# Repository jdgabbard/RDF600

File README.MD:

# RDF-600
 RDF-600 Floppy Adapter for MSX Computers.

***Based on the TDC-600***

This is a clone of the TDC-600 Disk Adadpter for MSX Computers redesigned for a more compact footprint.  This should fit inside standard MSX cartridge shells that have been modified to allow for the floppy ribbon cable.

The board is compatible with the standard TDC-600 firmware.  Or, if using an imported machine in the US or UK, it can be used with the provided firmware which has been patched for the English Language.

The Original Source Code for the PCB, and a working disassembly of it, can be found here:  https://github.com/jdgabbard/TDC-600-Source-Code

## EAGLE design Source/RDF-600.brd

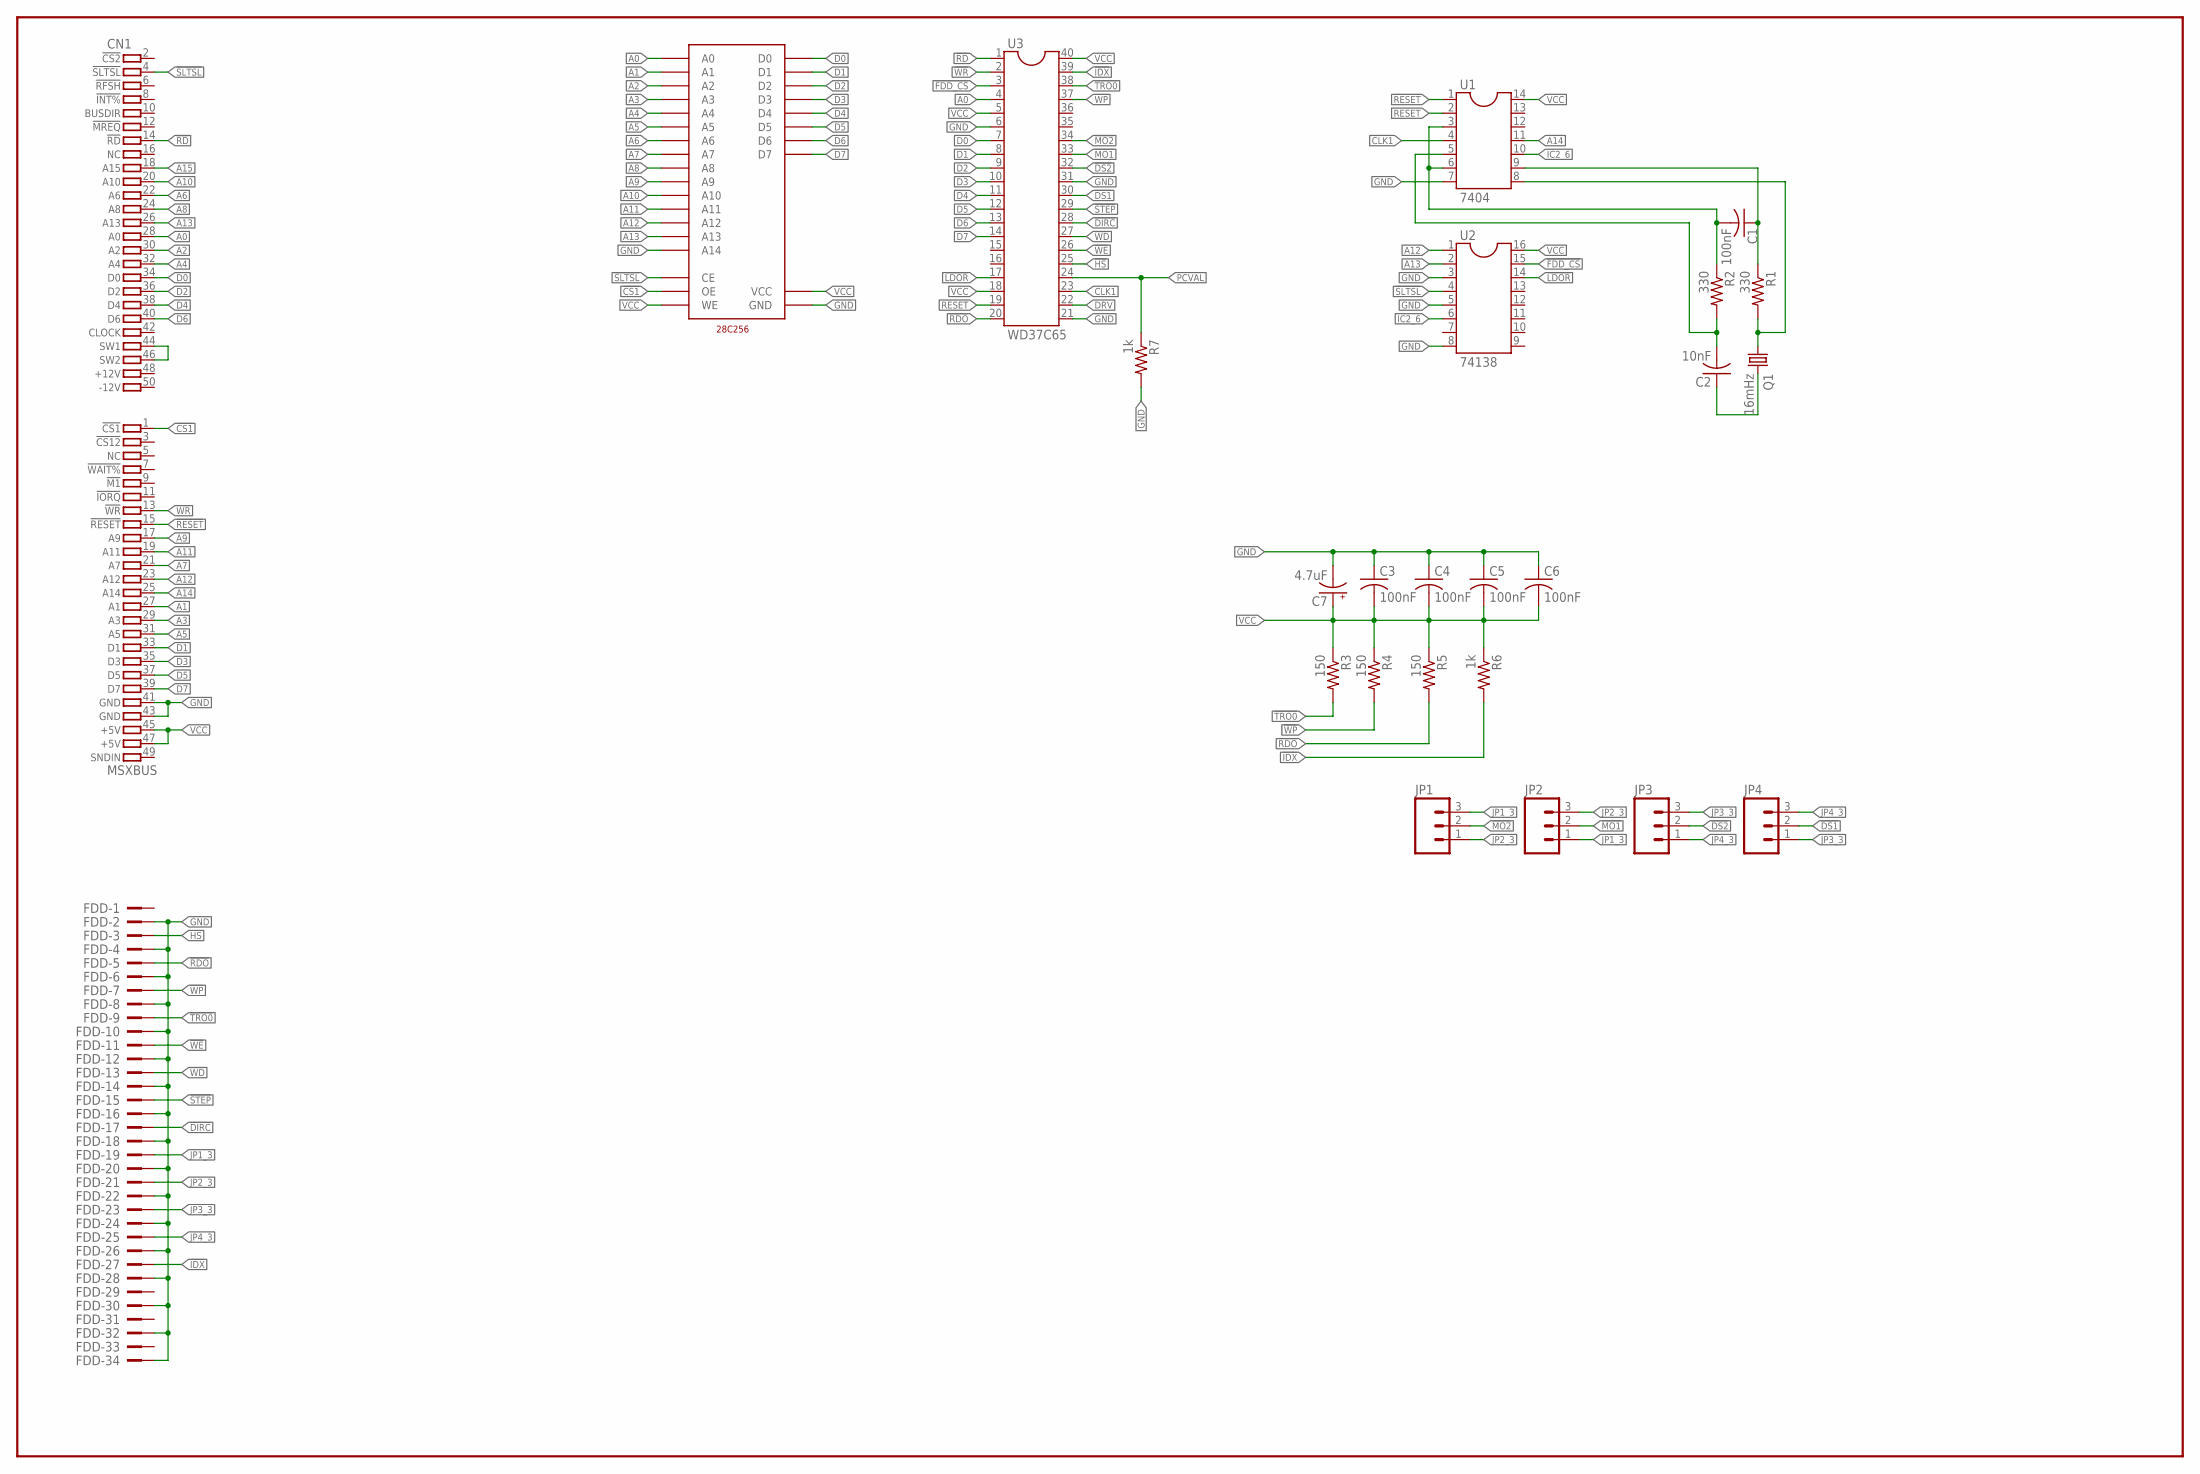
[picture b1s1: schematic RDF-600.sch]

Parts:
28C256: 28C256; DIP28
C1, C3, C4, C5, C6: 100nF; C025-025X050
C2: 10nF; C025-025X050
C7: 4.7uF; E2,5-6E
CN1: MSXBUS; MSXBUS_EDGECONN
FDD: 2534-5; PAK100/2500-5-34
JP1, JP2, JP3, JP4: M03PTH; 1X03
Q1: 16mHz; HC49/S
R1, R2: 330; 0207/7
R3, R4, R5: 150; 0207/7
R6, R7: 1k; 0207/7
U1: 7404; DIL14
U2: 74138; DIL16
U3: WD37C65; DIL40

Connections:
!CS1: 28C256.P$22 (OE), CN1.1 (1.!CS1)
!DIRC: FDD.17, U3.28
!DS1: JP4.2, U3.30
!DS2: JP3.2, U3.32
!FDD_CS: U2.15, U3.3
!HS: FDD.3, U3.25
!IDX: FDD.27, R6.2, U3.39
!LDOR: U2.14, U3.17
!MO1: JP2.2, U3.33
!MO2: JP1.2, U3.34
!RD: CN1.14 (14.!RD), U3.1
!RDO: FDD.5, R5.2, U3.20
!RESET: CN1.15 (15.!RESET), U1.1
!SLTSL: 28C256.P$20 (CE), CN1.4 (4.!SLTSL), U2.4
!STEP: FDD.15, U3.29
!TRO0: FDD.9, R3.2, U3.38
!WD: FDD.13, U3.27
!WE: FDD.11, U3.26
!WP: FDD.7, R4.2, U3.37
!WR: CN1.13 (13.!WR), U3.2
A0: 28C256.P$10 (A0), CN1.28 (28.A0), U3.4
A1: 28C256.P$9 (A1), CN1.27 (27.A1)
A2: 28C256.P$8 (A2), CN1.30 (30.A2)
A3: 28C256.P$7 (A3), CN1.29 (29.A3)
A4: 28C256.P$6 (A4), CN1.32 (32.A4)
A5: 28C256.P$5 (A5), CN1.31 (31.A5)
A6: 28C256.P$4 (A6), CN1.22 (22.A6)
A7: 28C256.P$3 (A7), CN1.21 (21.A7)
A8: 28C256.P$25 (A8), CN1.24 (24.A8)
A9: 28C256.P$24 (A9), CN1.17 (17.A9)
A10: 28C256.P$21 (A10), CN1.20 (20.A10)
A11: 28C256.P$23 (A11), CN1.19 (19.A11)
A12: 28C256.P$2 (A12), CN1.23 (23.A12), U2.1
A13: 28C256.P$26 (A13), CN1.26 (26.A13), U2.2
A14: CN1.25 (25.A14), U1.11
A15: CN1.18 (18.A15)
CLK1: U1.4, U3.23
D0: 28C256.P$11 (D0), CN1.34 (34.D0), U3.7
D1: 28C256.P$12 (D1), CN1.33 (33.D1), U3.8
D2: 28C256.P$13 (D2), CN1.36 (36.D2), U3.9
D3: 28C256.P$15 (D3), CN1.35 (35.D3), U3.10
D4: 28C256.P$16 (D4), CN1.38 (38.D4), U3.11
D5: 28C256.P$17 (D5), CN1.37 (37.D5), U3.12
D6: 28C256.P$18 (D6), CN1.40 (40.D6), U3.13
D7: 28C256.P$19 (D7), CN1.39 (39.D7), U3.14
DRV: U3.22
GND: 28C256.P$1 (A14), 28C256.P$14 (GND), C3.1, C4.1, C5.1, C6.1, C7.-, CN1.41 (41.GND), CN1.43 (43.GND), FDD.2, FDD.4, FDD.6, FDD.8, FDD.10, FDD.12, FDD.14, FDD.16, FDD.18, FDD.20, FDD.22, FDD.24, FDD.26, FDD.28, FDD.30, FDD.32, FDD.34, R7.2, U1.7, U2.3, U2.5, U2.8, U3.6, U3.21, U3.31
IC2_6: U1.10, U2.6
JP1_3: FDD.19, JP1.3, JP2.1
JP2_3: FDD.21, JP1.1, JP2.3
JP3_3: FDD.23, JP3.3, JP4.1
JP4_3: FDD.25, JP3.1, JP4.3
unnamed: Q1.1, R1.2, U1.8
unnamed: C2.1, Q1.2
unnamed: C2.2, R2.2, U1.5
unnamed: C1.1, R1.1, U1.9
unnamed: C1.2, R2.1, U1.3, U1.6
unnamed: CN1.44 (44.SW1), CN1.46 (46.SW2)
PCVAL: R7.1, U3.24
RESET: U1.2, U3.19
VCC: 28C256.P$27 (WE), 28C256.P$28 (VCC), C3.2, C4.2, C5.2, C6.2, C7.+, CN1.45 (45.+5V), CN1.47 (47.+5V), R3.1, R4.1, R5.1, R6.1, U1.14, U2.16, U3.5, U3.18, U3.40

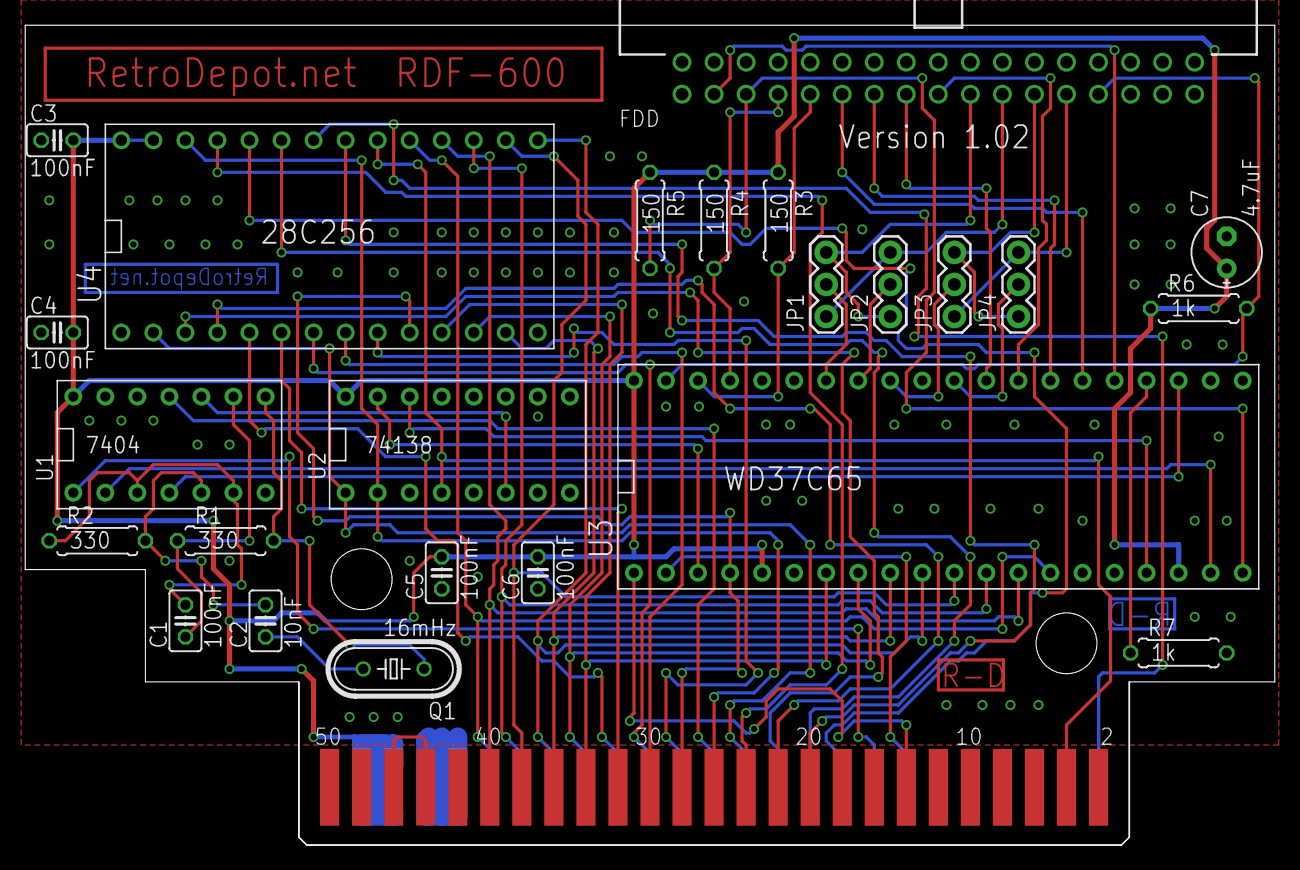
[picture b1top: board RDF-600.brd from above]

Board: 2 copper layers, 99.1 x 65.0 mm, 25 parts (0 on the bottom side), 59 nets.

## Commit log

2022-09-09 Initial Upload

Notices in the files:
parts and their libraries:
SparkFun-Connectors: Licensing: Creative Commons ShareAlike 4.0 International - https://creativecommons.org/licenses/by-sa/4.0
